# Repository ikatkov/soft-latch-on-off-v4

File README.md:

https://www.falstad.com/circuit/circuitjs.html?ctz=CQAgjCAMB0l3BWcA2Z0DMAWA7ATnQEyYAc6hY2yIykISm6dApgLRhgBQAZiMXCAUjEQ2dFUHDCA6FRiQC3EWPCZMSqiRCYIBaGrkKATr00SQuSgKFQt2eJA4B3EYK3DkRN1CfVPmhDReDs4BtJraGsKcxqEqarGatGD2DsYW4tbpQeApPtgIBF7E4cLB6nHlYLiFDgDmvPzokGp8tGSy3s7FwppZmtHgRD1RQ+DVNslwHGAeg-3jYKPoBQIgACZMXACGAK4ANgAuLHtMa+A2tHKc9Yuay4W3PTMXHABKWs93zdlhSTUX0AQHAAxiZhmCrKUoLB7ARCphoKI4XxcGAEJhBJRZDDOKCPGpNPiKpcYfAICwYAhmuwsBiCLhtMRRNC4AMIhV2YkcvAQR8qGBVHRAgL9Cz7OTKWQwKR6bhcMgAqokHJIJwQsLBUSRd4zpzws9tYUNtt9gcfFkzH1EubLKonhprQBnAQBDkGwVJEDbPaOpgceoEV0EbCFQNUe4vYxhgQhl38j3gHyPLx9UocAAeOU86FwOT4WnhAjUADUADqOgD2OzNmYIOYL4cwYXpWiLIAAsgBhACq5YACgBJAByPi1gtE8f0vO6kIhTVFYFY2BALHQiKEYjrwew2AFpH0OJ8rVnM7MqQatDMx-nExSZRnN+v33vjW+E5AN7K75v77hU8z6CLOcmCBASbZlo6ACWAB25YABRrugLCCMWACUGbgOwvDCHWuaoq2ngAA6GEwjqOuWBwVuWADyI6ZtogxIEQ-IED0bYABYVnsazlgQq6+sCFFUY61EAGKiT47LajeTaXBhO5aMgkh2LYEBqER+x7OWAAy1EAOrllwFaGLx-FMIJjqUTR4nycQEDsMupBIIsYSDCAByQQAtjBtTlsCWyERwABG1DEFC2CkAIswOJmdiFCwubYCBK4aG5ACC1EgYIHBAA

original http://www.mosaic-industries.com/embedded-systems/microcontroller-projects/raspberry-pi/on-off-power-controller

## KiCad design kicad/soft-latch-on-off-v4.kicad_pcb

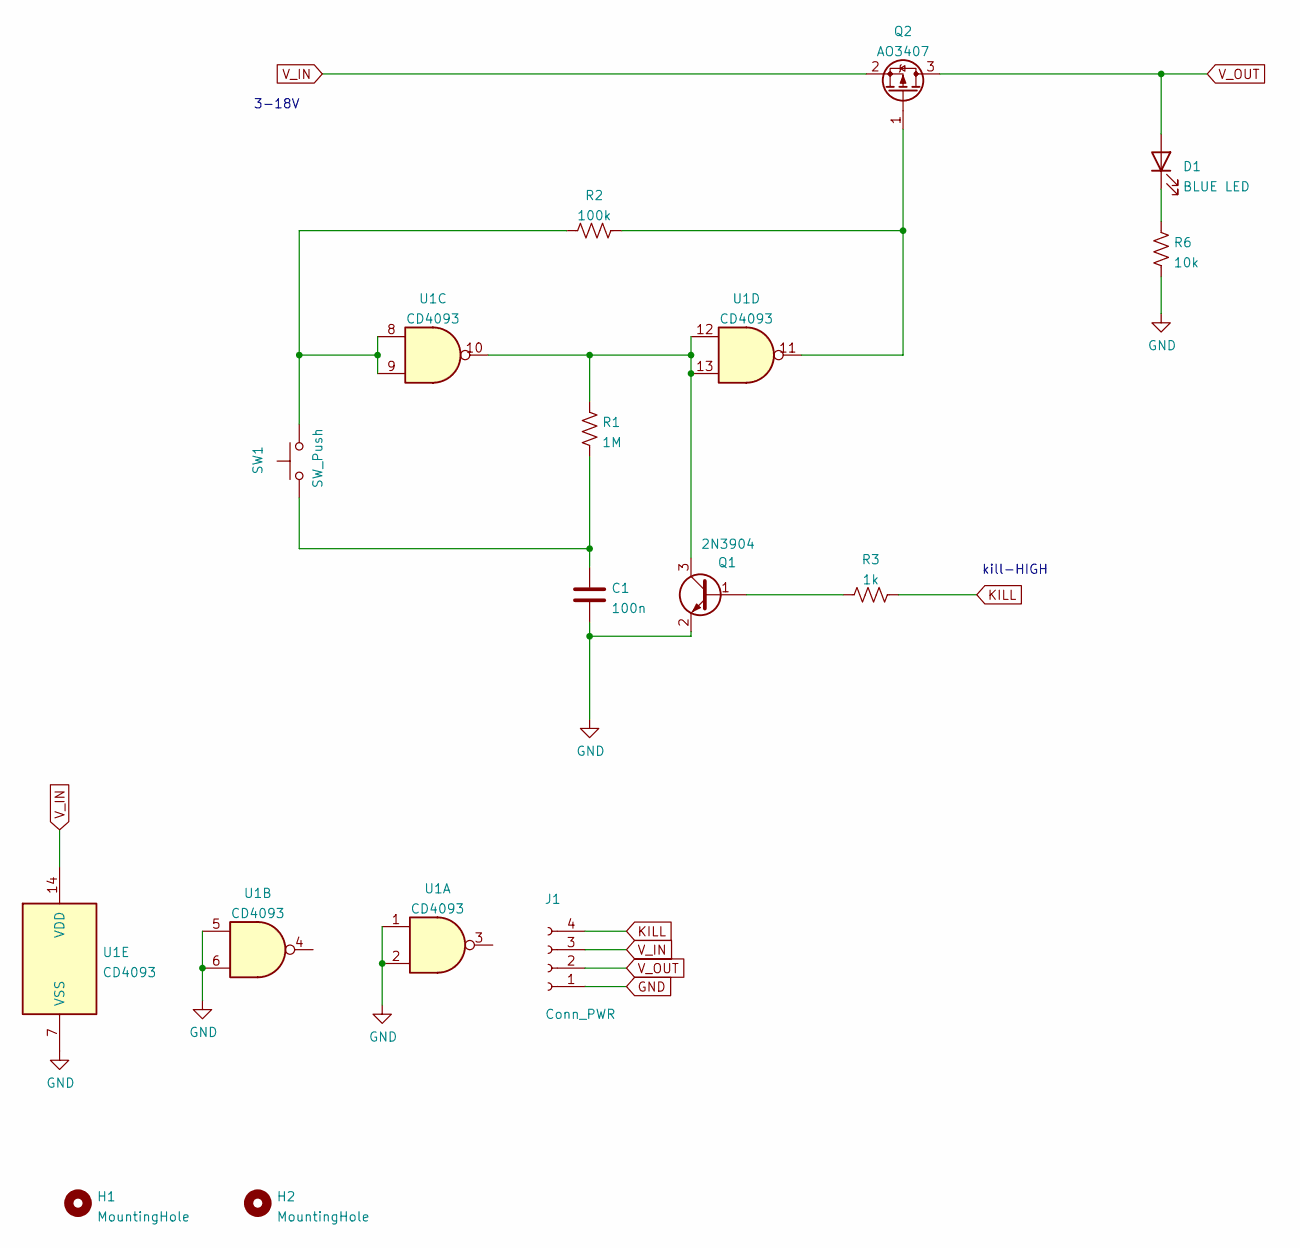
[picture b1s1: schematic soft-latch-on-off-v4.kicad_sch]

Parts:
C1: 100n; C_1206_3216Metric
D1: BLUE LED; LED_0805_2012Metric_Pad1.15x1.40mm_HandSolder
H1, H2: MountingHole; MountingHole_2.7mm_M2.5
J1: Conn_PWR; PinHeader_1x04_P2.54mm_Vertical
Q1: 2N3904; SOT-23
Q2: AO3407; SOT-23
R1: 1M; R_0805_2012Metric_Pad1.20x1.40mm_HandSolder
R2: 100k; R_0805_2012Metric_Pad1.20x1.40mm_HandSolder
R3: 1k; R_0805_2012Metric_Pad1.20x1.40mm_HandSolder
R6: 10k; R_0805_2012Metric_Pad1.20x1.40mm_HandSolder
SW1: SW_Push; SW_PUSH_6mm
U1: CD4093; SOIC-14_3.9x8.7mm_P1.27mm

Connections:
GND: C1.2, J1.1, Q1.2 (E), R6.2, U1.1, U1.2, U1.5, U1.6, U1.7 (VSS)
KILL: J1.4, R3.1
unnamed: C1.1, R1.1, SW1.1
unnamed: D1.1 (K), R6.1
unnamed: Q2.1 (G), R2.2, U1.11
unnamed: Q1.3 (C), R1.2, U1.10, U1.12, U1.13
unnamed: R2.1, SW1.2, U1.8, U1.9
unnamed: Q1.1 (B), R3.2
V_IN: J1.3, Q2.2 (S), U1.14 (VDD)
V_OUT: D1.2 (A), J1.2, Q2.3 (D)

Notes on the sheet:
kill-HIGH
3-18V

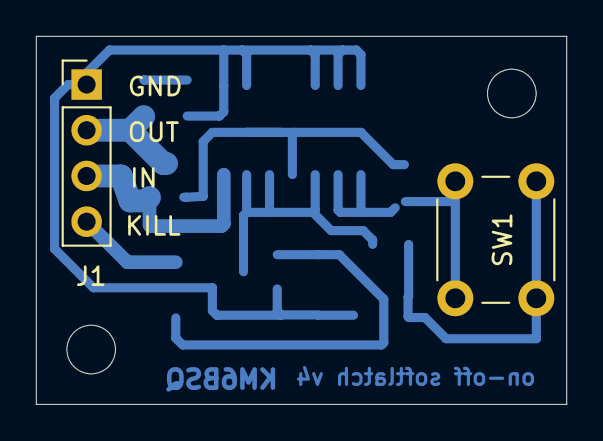
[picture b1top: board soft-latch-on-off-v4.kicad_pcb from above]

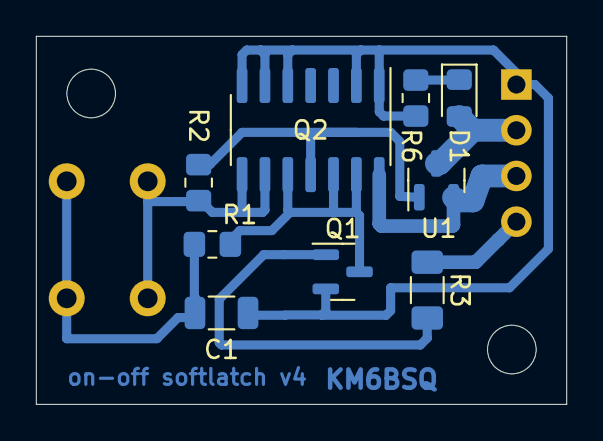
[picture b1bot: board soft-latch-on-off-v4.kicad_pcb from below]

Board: 2 copper layers, 29.5 x 20.4 mm, 13 parts (9 on the bottom side), 10 nets.

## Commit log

2022-08-01 Initial
